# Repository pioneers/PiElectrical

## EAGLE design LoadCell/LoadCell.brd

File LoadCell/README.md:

#Load Cell

Detects the weight of an object

[HX711](https://www.sparkfun.com/products/13879) which interfaces with a loadcell

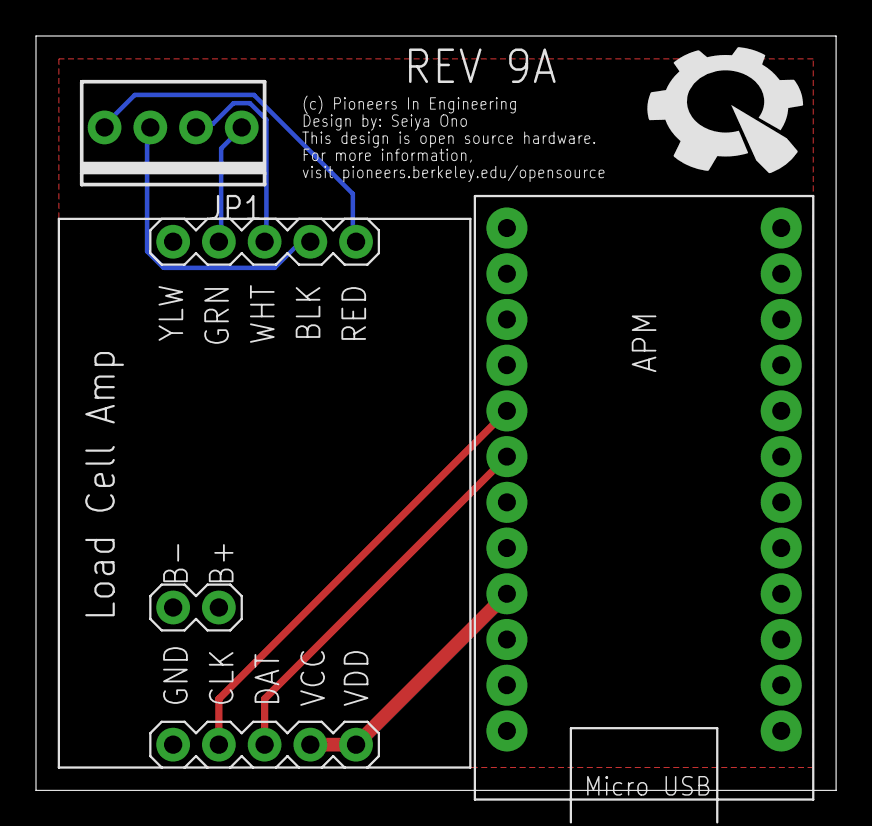
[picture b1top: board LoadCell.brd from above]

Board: 2 copper layers, 44.5 x 41.9 mm, 4 parts (0 on the bottom side), 8 nets.

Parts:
APM: ARDUINO_PRO_MICRO
IC1: LOADCELL_AMP
JP1: 1X04-MTA
U$3: PIE-LOGO-SMALL

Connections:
CLK: APM.A0, IC1.CLK
DAT: APM.A1, IC1.DAT
GND: APM.GND@1, IC1.GND
unnamed: IC1.BLK, JP1.3
unnamed: IC1.RED, JP1.4
unnamed: IC1.WHT, JP1.2
unnamed: IC1.GRN, JP1.1
VCC: APM.VCC, IC1.VCC, IC1.VDD

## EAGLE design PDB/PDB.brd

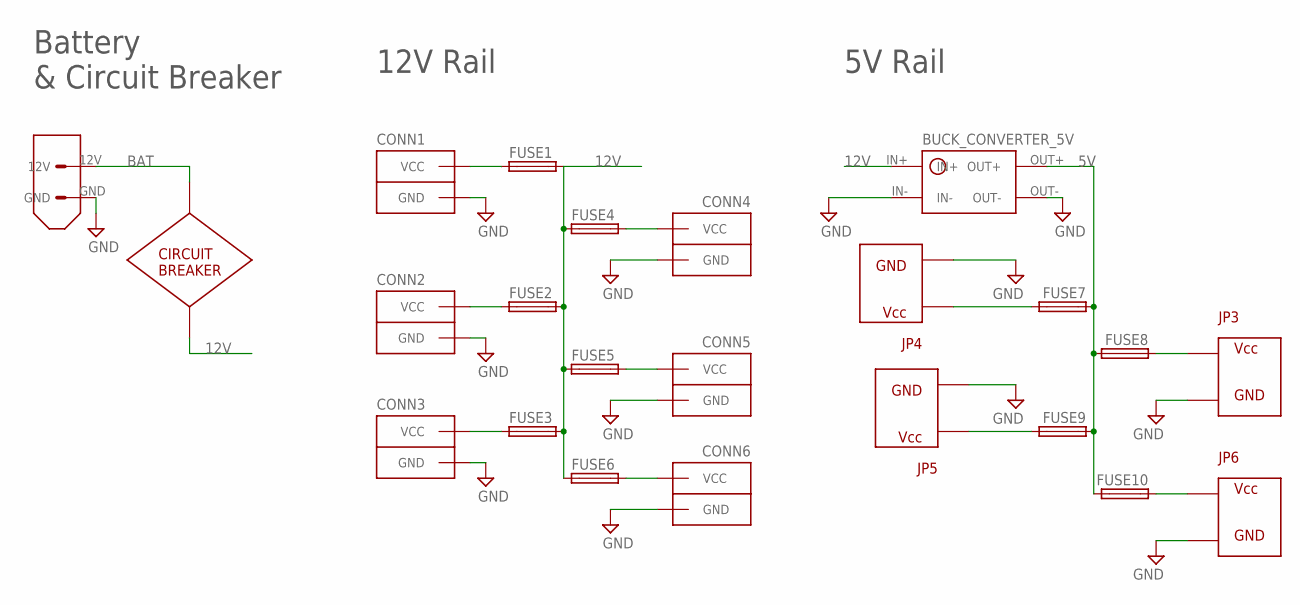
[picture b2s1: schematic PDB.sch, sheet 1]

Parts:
CIRCUIT_BREAKER: CIRC_BREAKER
CONN1, CONN2, CONN3, CONN4, CONN5, CONN6: ANDERSONVERTICAL; ANDERSON_VERTICAL
FUSE1, FUSE2, FUSE3, FUSE4, FUSE5, FUSE6, FUSE7, FUSE8, FUSE9, FUSE10: FUSE_HOLDER_SMD
JP3, JP4, JP5, JP6: ATX
U$7: BUCK_CONVERTER_5V
XT60: XT60CONNECTOR

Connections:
5V: FUSE7.P$1_DOWN (1), FUSE7.P$1_UP (1), FUSE8.P$2_DOWN (2), FUSE8.P$2_UP (2), FUSE9.P$1_DOWN (1), FUSE9.P$1_UP (1), FUSE10.P$2_DOWN (2), FUSE10.P$2_UP (2), U$7.OUT+; also elsewhere on the board
12V: CIRCUIT_BREAKER.P$2, FUSE1.P$2_DOWN (2), FUSE1.P$2_UP (2), FUSE2.P$2_DOWN (2), FUSE2.P$2_UP (2), FUSE3.P$2_DOWN (2), FUSE3.P$2_UP (2), FUSE4.P$1_DOWN (1), FUSE4.P$1_UP (1), FUSE5.P$1_DOWN (1), FUSE5.P$1_UP (1), FUSE6.P$1_DOWN (1), FUSE6.P$1_UP (1), U$7.IN+
BAT: CIRCUIT_BREAKER.P$1, XT60.12V
BCELL1: JP3.2; also elsewhere on the board
BCELL2: JP3.3; also elsewhere on the board
BCELL3: JP3.4; also elsewhere on the board
BGND: JP3.1; also elsewhere on the board
GND: CONN1.PIN1 (GND), CONN2.PIN1 (GND), CONN3.PIN1 (GND), CONN4.PIN1 (GND), CONN5.PIN1 (GND), CONN6.PIN1 (GND), JP3.P$2, JP4.P$2, JP5.P$2, JP6.P$2, U$7.IN-, U$7.OUT-, XT60.GND; also elsewhere on the board
VOUT1: CONN1.PIN2 (VCC), FUSE1.P$1_DOWN (1), FUSE1.P$1_UP (1)
VOUT2: CONN2.PIN2 (VCC), FUSE2.P$1_DOWN (1), FUSE2.P$1_UP (1)
VOUT3: CONN3.PIN2 (VCC), FUSE3.P$1_DOWN (1), FUSE3.P$1_UP (1)
VOUT4: CONN4.PIN2 (VCC), FUSE4.P$2_DOWN (2), FUSE4.P$2_UP (2)
VOUT5: CONN5.PIN2 (VCC), FUSE5.P$2_DOWN (2), FUSE5.P$2_UP (2)
VOUT6: CONN6.PIN2 (VCC), FUSE6.P$2_DOWN (2), FUSE6.P$2_UP (2)
VOUT7: FUSE7.P$2_DOWN (2), FUSE7.P$2_UP (2), JP4.P$1; also elsewhere on the board
VOUT8: FUSE8.P$1_DOWN (1), FUSE8.P$1_UP (1), JP3.P$1; also elsewhere on the board
VOUT9: FUSE9.P$2_DOWN (2), FUSE9.P$2_UP (2), JP5.P$1; also elsewhere on the board
VOUT10: FUSE10.P$1_DOWN (1), FUSE10.P$1_UP (1), JP6.P$1; also elsewhere on the board

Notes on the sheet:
Battery & Circuit Breaker
12V Rail
5V Rail

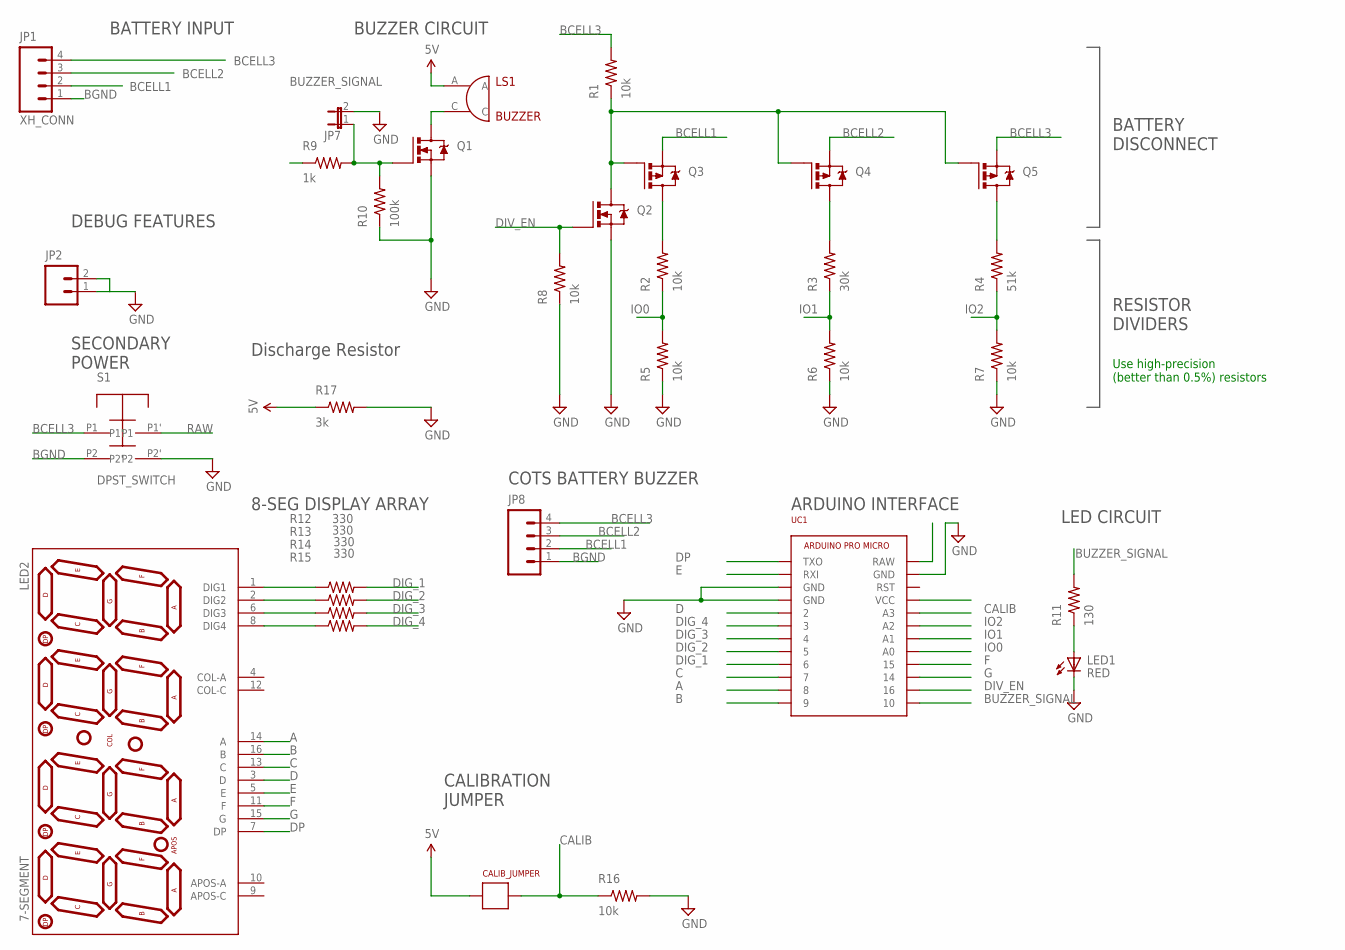
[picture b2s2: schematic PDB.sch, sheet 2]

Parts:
CALIB_JUMPER: JUMPER
JP1: XH_CONN; XH_CONNECTOR_4POS_2.5MM
JP2: M02PTH; 1X02
JP7: JP1E; JP1
JP8: M04PTH; 1X04
LED1: RED; LED-0805
LED2: 7-SEGMENT; 7-SEGMENT-4DIGIT-YOUNGSUN
LS1: BUZZER; BUZZER_MAGNETIC_5V_12MM_RADIAL
Q1: NMOS; SOT23-3
Q2: IRFML8244; SOT23-3
Q3, Q4, Q5: PMOS; SOT23-3
R1, R2, R5, R6, R7, R8, R16: 10k; R0603
R3: 30k; R0603
R4: 51k; R0603
R9: 1k; R0603
R10: 100k; R0603
R11: 130; R0603
R12, R13, R14, R15: 330; R0603
R17: 3k; R0603
S1: DPST_SWITCH; C&K_SWITCH
UC1: ARDUINO_PRO_MICRO

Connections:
5V: CALIB_JUMPER.P$1, LS1.A, R17.1, UC1.VCC; also elsewhere on the board
A: LED2.14 (A), UC1.8
B: LED2.16 (B), UC1.9
BCELL1: JP1.2, JP8.2, Q3.2 (S); also elsewhere on the board
BCELL2: JP1.3, JP8.3, Q4.2 (S); also elsewhere on the board
BCELL3: JP1.4, JP8.4, Q5.2 (S), R1.2, S1.P1; also elsewhere on the board
BGND: JP1.1, JP8.1, S1.P2; also elsewhere on the board
BUZZER_SIGNAL: R9.1, R11.2, UC1.10
C: LED2.13 (C), UC1.7
CALIB: CALIB_JUMPER.P$2, R16.1, UC1.A3
D: LED2.3 (D), UC1.2
DIG_1: R12.2, UC1.6
DIG_2: R13.2, UC1.5
DIG_3: R14.2, UC1.4
DIG_4: R15.2, UC1.3
DIV_EN: Q2.1 (G), R8.2, UC1.16
DP: LED2.7 (DP), UC1.TXO
E: LED2.5 (E), UC1.RXI
F: LED2.11 (F), UC1.15
G: LED2.15 (G), UC1.14
GND: JP2.1, JP2.2, JP7.2, LED1.C, Q1.2 (S), Q2.2 (S), R5.1, R6.1, R7.1, R8.1, R10.1, R16.2, R17.2, S1.P2', UC1.GND@0 (GND), UC1.GND@1 (GND), UC1.GND@2 (GND); also elsewhere on the board
IO0: R2.1, R5.2, UC1.A0
IO1: R3.1, R6.2, UC1.A1
IO2: R4.1, R7.2, UC1.A2
unnamed: Q2.3 (D), Q3.1 (G), Q4.1 (G), Q5.1 (G), R1.1
unnamed: Q3.3 (D), R2.2
unnamed: Q4.3 (D), R3.2
unnamed: Q5.3 (D), R4.2
unnamed: LS1.C, Q1.3 (D)
unnamed: JP7.1, Q1.1 (G), R9.2, R10.2
unnamed: LED1.A, R11.1
unnamed: LED2.1 (DIG1), R12.1
unnamed: LED2.2 (DIG2), R13.1
unnamed: LED2.6 (DIG3), R14.1
unnamed: LED2.8 (DIG4), R15.1
RAW: S1.P1', UC1.RAW

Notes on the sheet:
ARDUINO INTERFACE
LED CIRCUIT
BUZZER CIRCUIT
BATTERY INPUT
BATTERY DISCONNECT
RESISTOR DIVIDERS
Use high-precision (better than 0.5%) resistors
CALIBRATION JUMPER
SECONDARY POWER
8-SEG DISPLAY ARRAY
DEBUG FEATURES
Discharge Resistor
COTS BATTERY BUZZER

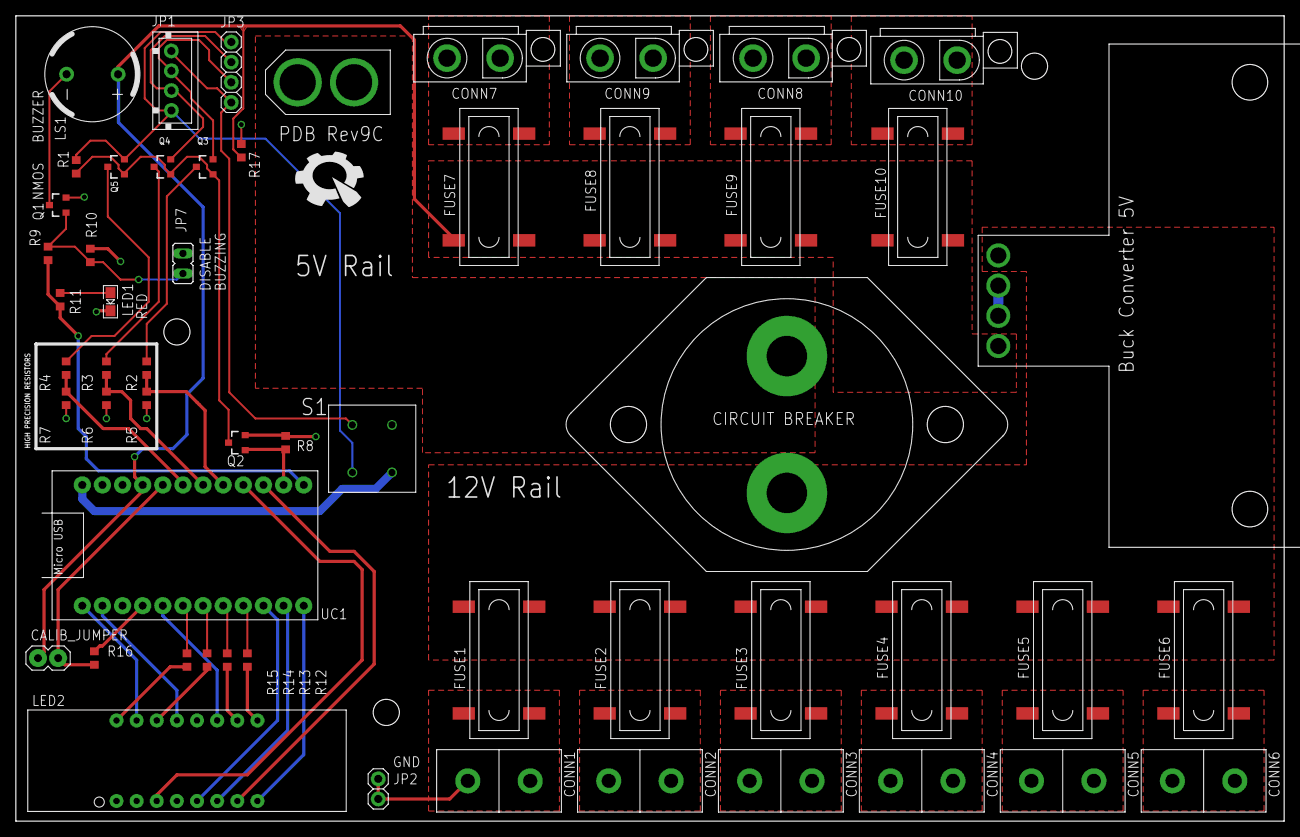
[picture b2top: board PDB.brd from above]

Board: 2 copper layers, 160.0 x 101.6 mm, 59 parts (0 on the bottom side), 48 nets.

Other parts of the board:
CONN7, CONN8, CONN9, CONN10: ATX
U$2, U$4, U$5: STAND-OFF
U$6: PIE-LOGO-SMALL

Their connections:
GND: CONN7.P$2, CONN8.P$2, CONN9.P$2, CONN10.P$2; also elsewhere on the board
VOUT7: CONN7.P$1; also elsewhere on the board
VOUT8: CONN9.P$1; also elsewhere on the board
VOUT9: CONN8.P$1; also elsewhere on the board
VOUT10: CONN10.P$1; also elsewhere on the board

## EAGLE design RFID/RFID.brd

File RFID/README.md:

#RFID

Identifies [RFID chips](https://www.aliexpress.com/item/High-Quality-MFRC-522-RC522-RFID-Reader-RF-IC-Card-Inductive-Sensor-Module-For-Arduino-Module/32657638702.html?spm=2114.01010208.3.1.ePefNj&ws_ab_test=searchweb201556_0%2Csearchweb201602_5_10057_10056_10065_10068_10055_10067_10054_10069_10059_10058_418_10073_10017_10070_10060_10061_10052_10062_10053_10050_10051%2Csearchweb201603_7&btsid=cb39fcb9-9ace-4eec-a43a-83949f44e6b2)

[Documentation](https://github.com/miguelbalboa/rfid)

Starting for Rev B

Pinouts:

RFID | Arduino Pro Micro
---- | -----------------
RST | RST
SDA | 10
MOSI | 16
MISO | 14
SCK | 15
3.3V | VCC
GND | GND

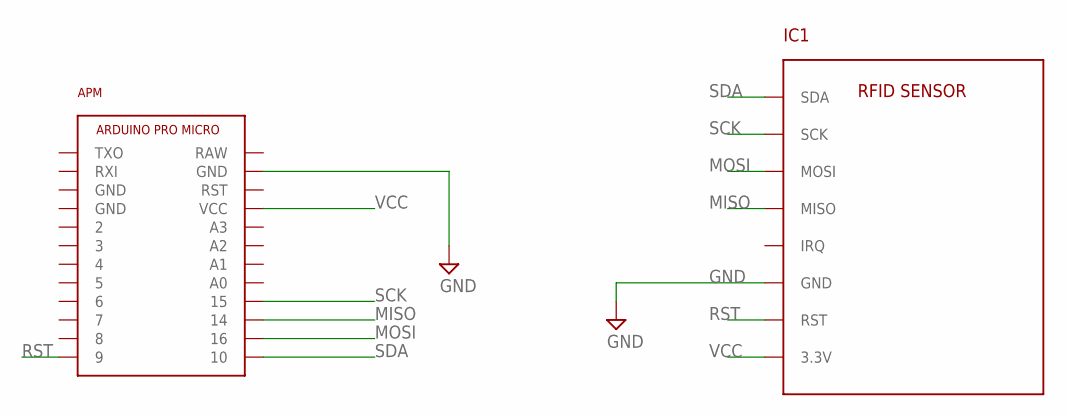
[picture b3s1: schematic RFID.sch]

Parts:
APM: ARDUINO_PRO_MICRO
IC1: RFID_SENSOR

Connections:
GND: APM.GND@2 (GND), IC1.GND
MISO: APM.14, IC1.MISO
MOSI: APM.16, IC1.MOSI
RST: APM.9, IC1.RST
SCK: APM.15, IC1.SCK
SDA: APM.10, IC1.SDA
VCC: APM.VCC, IC1.3.3V

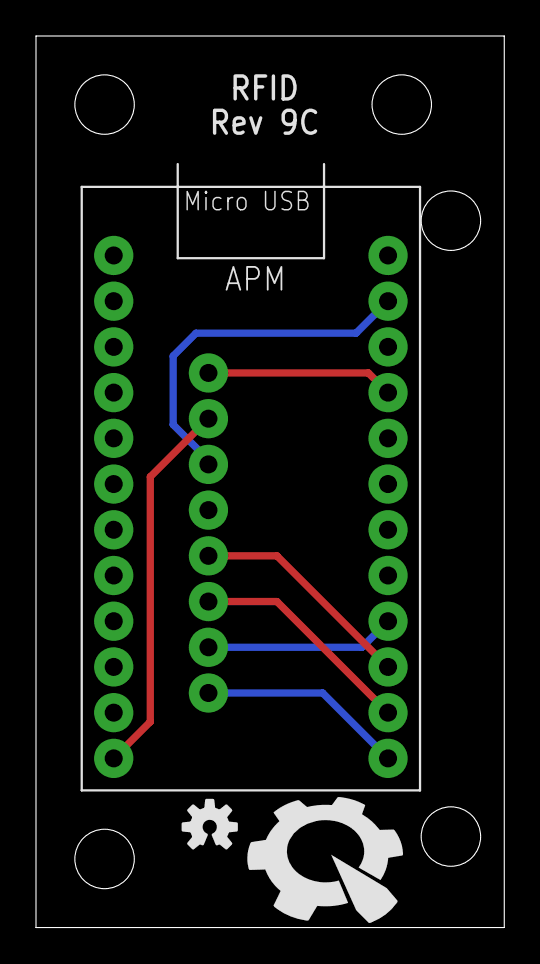
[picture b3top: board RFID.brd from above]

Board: 2 copper layers, 26.0 x 49.5 mm, 7 parts (1 on the bottom side), 7 nets.

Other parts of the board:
U$1: PIE-LOGO-SMALL
U$2, U$3, U$4: STAND-OFF
U$5: OSHW-LOGO-S

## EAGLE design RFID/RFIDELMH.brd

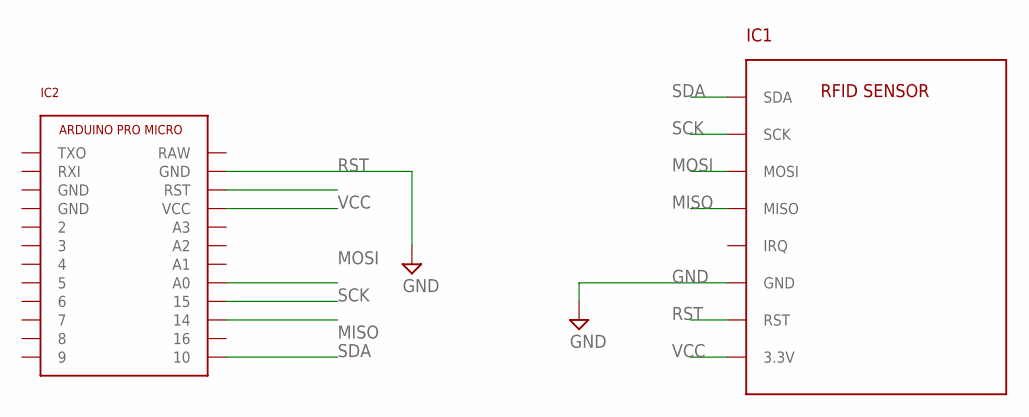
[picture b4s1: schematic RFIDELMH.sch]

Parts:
IC1: RFID_SENSOR
IC2: ARDUINO_PRO_MICRO

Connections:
GND: IC1.GND, IC2.GND@2 (GND)
MISO: IC1.MISO, IC2.14
MOSI: IC1.MOSI, IC2.A0
RST: IC1.RST, IC2.RST
SCK: IC1.SCK, IC2.15
SDA: IC1.SDA, IC2.10
VCC: IC1.3.3V, IC2.VCC

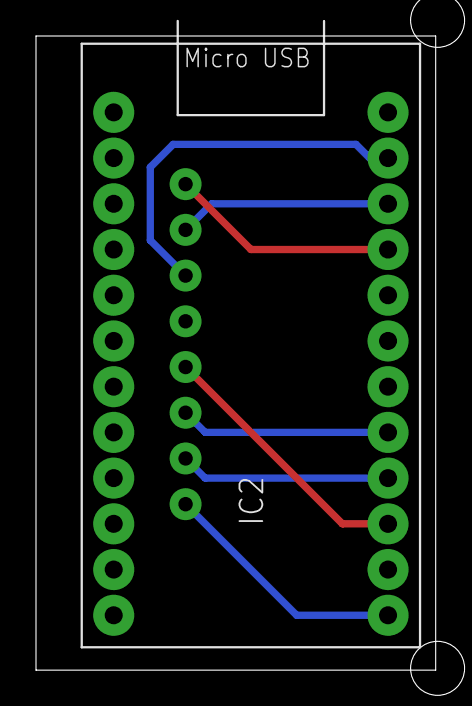
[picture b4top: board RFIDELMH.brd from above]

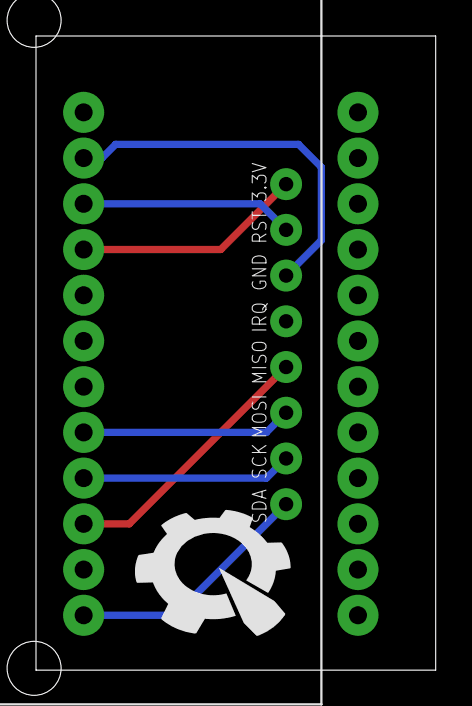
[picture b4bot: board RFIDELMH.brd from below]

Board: 2 copper layers, 22.2 x 35.2 mm, 3 parts (2 on the bottom side), 7 nets.

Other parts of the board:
U$1: PIE-LOGO-SMALL

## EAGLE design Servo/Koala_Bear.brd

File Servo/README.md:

#Servo Controller

Previous Named Koala Bear, controls the servo

Has 2 Servo Mounts, external 5 V and Max 1 Amp

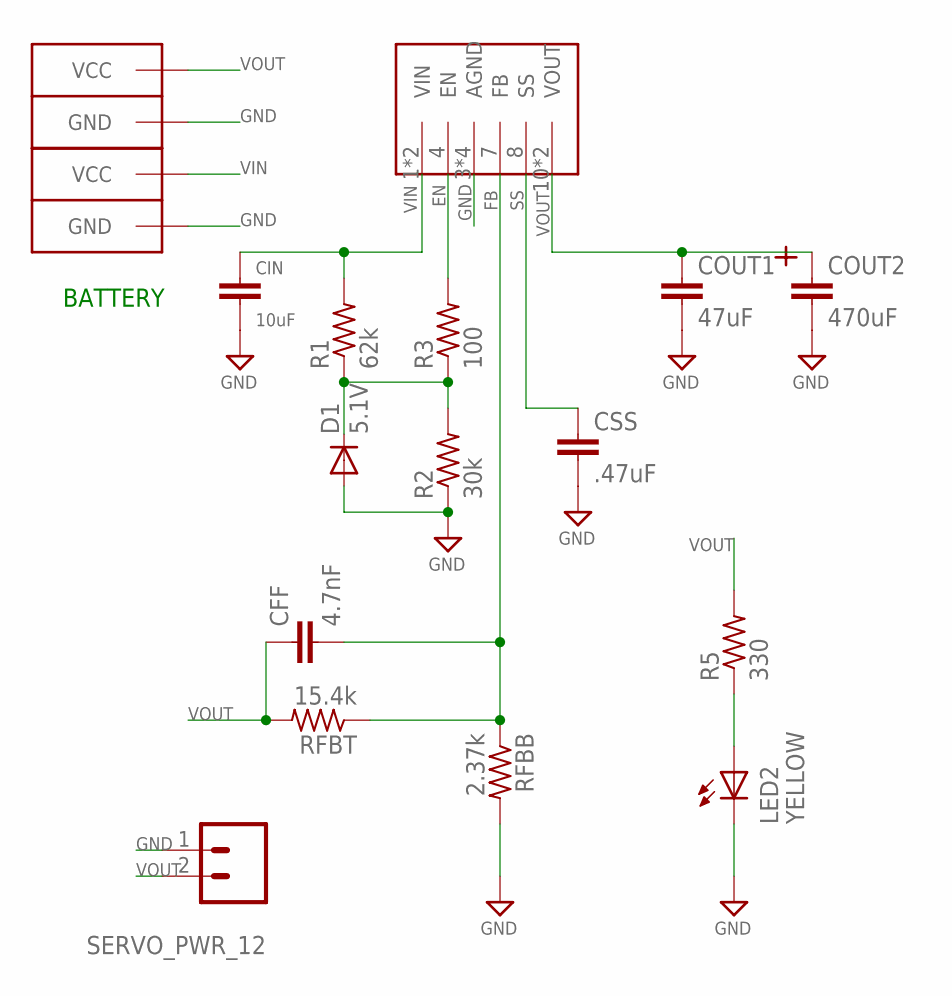
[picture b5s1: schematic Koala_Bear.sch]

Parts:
CFF: 4.7nF; 0603-CAP
CIN: 10uF; 1206
COUT1: 47uF; 1206
COUT2: 470uF; TANT_CASE_E
CSS: .47uF; 0603-CAP
D1: 5.1V; SOD-323
LED2: YELLOW; LED-0805
PWR, PWR1: ANDERSONVERTICAL; ANDERSON_VERTICAL
R1: 62k; R0603
R2: 30k; R0603
R3: 100; R0603
R5: 330; R0603
RFBB: 2.37k; R0603
RFBT: 15.4k; R0603
SERVO_PWR_12: M02PTH; 1X02
U$1: LMZ12010

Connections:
DIODE: D1.2 (C), R1.1, R2.2, R3.1
EN: R3.2, U$1.4 (EN)
FB: CFF.2, RFBB.1, RFBT.1, U$1.7 (FB)
GND: CIN.2, COUT1.2, COUT2.NEG, CSS.2, D1.1 (A), LED2.C, PWR.PIN1 (GND), PWR1.PIN1 (GND), R2.1, RFBB.2, SERVO_PWR_12.1, U$1.3 (AGND), U$1.5 (AGND), U$1.6 (AGND), U$1.GND (AGND)
unnamed: LED2.A, R5.1
SS: CSS.1, U$1.8 (SS)
VIN: CIN.1, PWR.PIN2 (VCC), R1.2, U$1.1 (VIN), U$1.2 (VIN)
VOUT: CFF.1, COUT1.1, COUT2.POS, PWR1.PIN2 (VCC), R5.2, RFBT.2, SERVO_PWR_12.2, U$1.10 (VOUT), U$1.11 (VOUT)

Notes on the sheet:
BATTERY

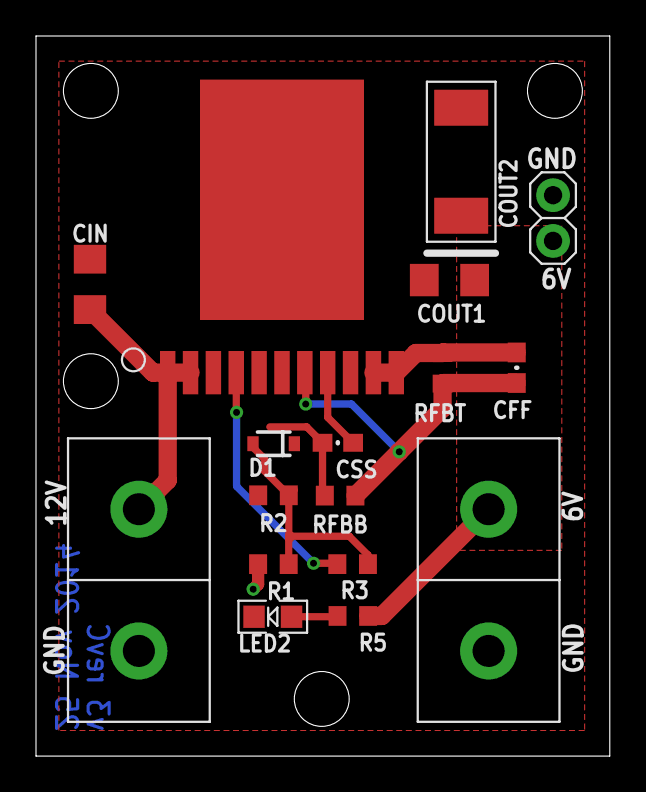
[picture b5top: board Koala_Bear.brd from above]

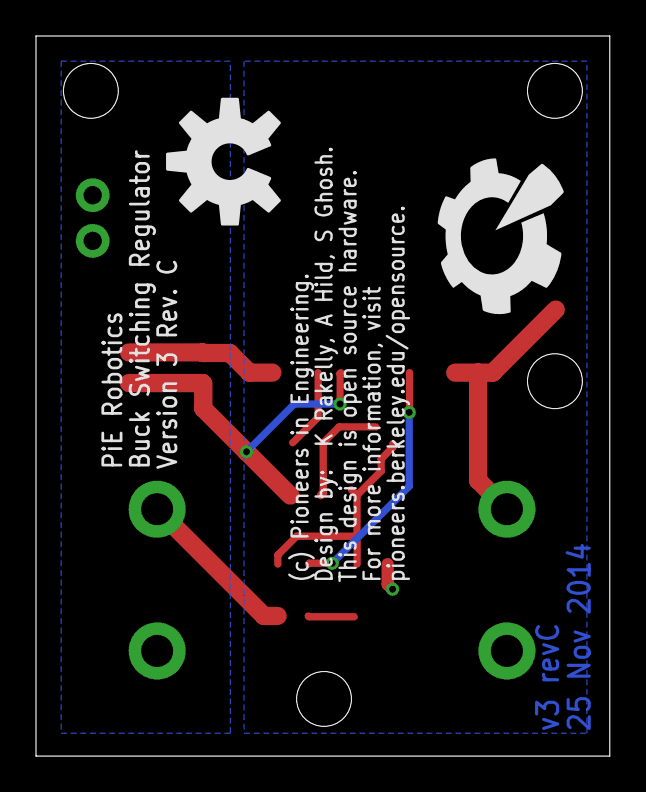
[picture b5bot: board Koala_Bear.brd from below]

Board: 2 copper layers, 31.9 x 40.0 mm, 23 parts (2 on the bottom side), 8 nets.

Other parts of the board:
U$2, U$3, U$4, U$5: STAND-OFF-TIGHT
U$10: PIE-LOGO-SMALL
U$11: OSHW-LOGO-L

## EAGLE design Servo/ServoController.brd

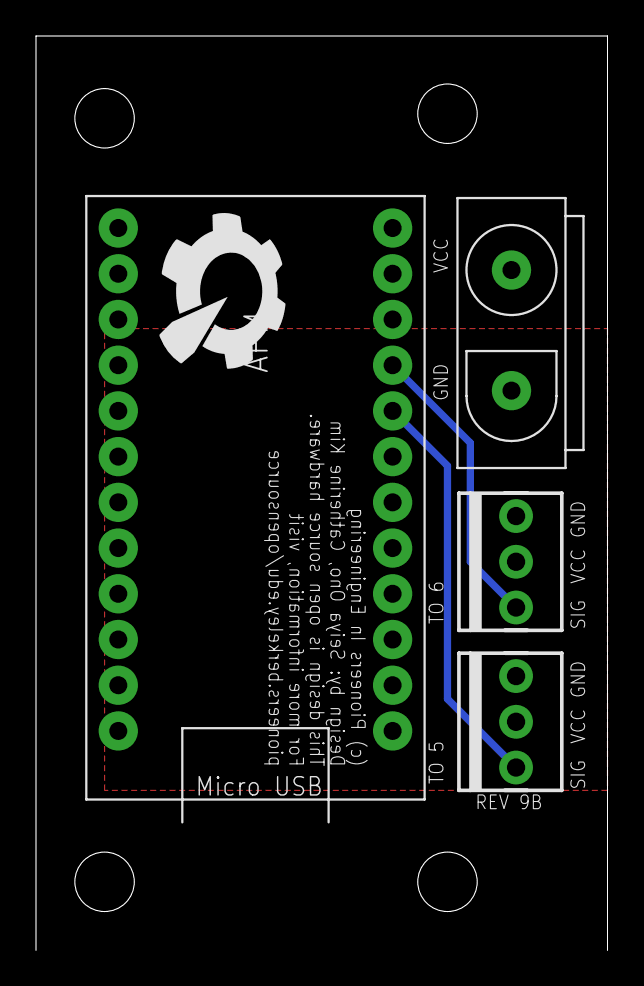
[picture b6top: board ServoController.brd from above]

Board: 2 copper layers, 31.8 x 50.8 mm, 9 parts (0 on the bottom side), 4 nets.

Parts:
APM: ARDUINO_PRO_MICRO
JP1, JP2: 1X03-MTA
JP3: ATX
U$1, U$3, U$4, U$5: STAND-OFF
U$2: PIE-LOGO-SMALL

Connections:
GND: APM.GND@0, APM.GND@1, APM.GND@2, JP1.3, JP2.3, JP3.P$2
SIG1: APM.5, JP1.1
SIG2: APM.6, JP2.1
VCC: JP1.2, JP2.2, JP3.P$1

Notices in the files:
PDB/PDB.brd:
Copyright (c) 2016, Pioneers in Engineering
All rights reserved.
